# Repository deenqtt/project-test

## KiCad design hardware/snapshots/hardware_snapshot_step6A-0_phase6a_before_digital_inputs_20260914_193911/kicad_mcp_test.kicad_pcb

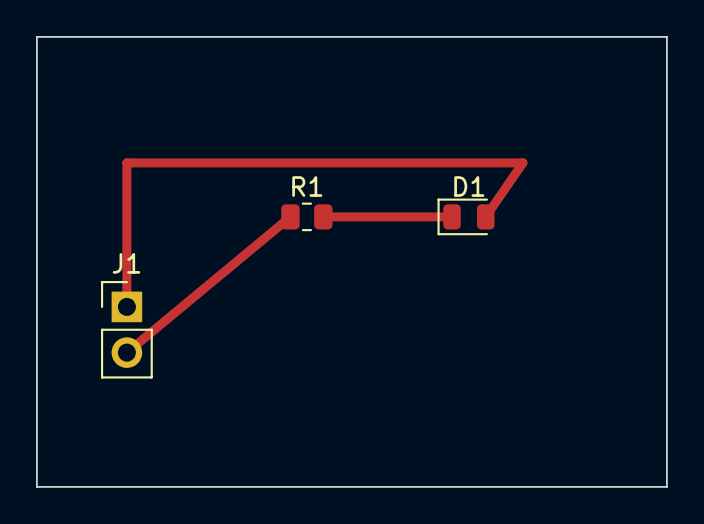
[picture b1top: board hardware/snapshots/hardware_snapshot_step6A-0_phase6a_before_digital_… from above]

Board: 2 copper layers, 35.0 x 25.0 mm, 3 parts (0 on the bottom side), 3 nets.

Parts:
D1: LED; LED_0805_2012Metric
J1: INPUT; PinHeader_1x02_P2.54mm_Vertical
R1: 1k; R_0805_2012Metric

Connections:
unnamed: D1.1, R1.2
unnamed: D1.2, J1.1
unnamed: J1.2, R1.1

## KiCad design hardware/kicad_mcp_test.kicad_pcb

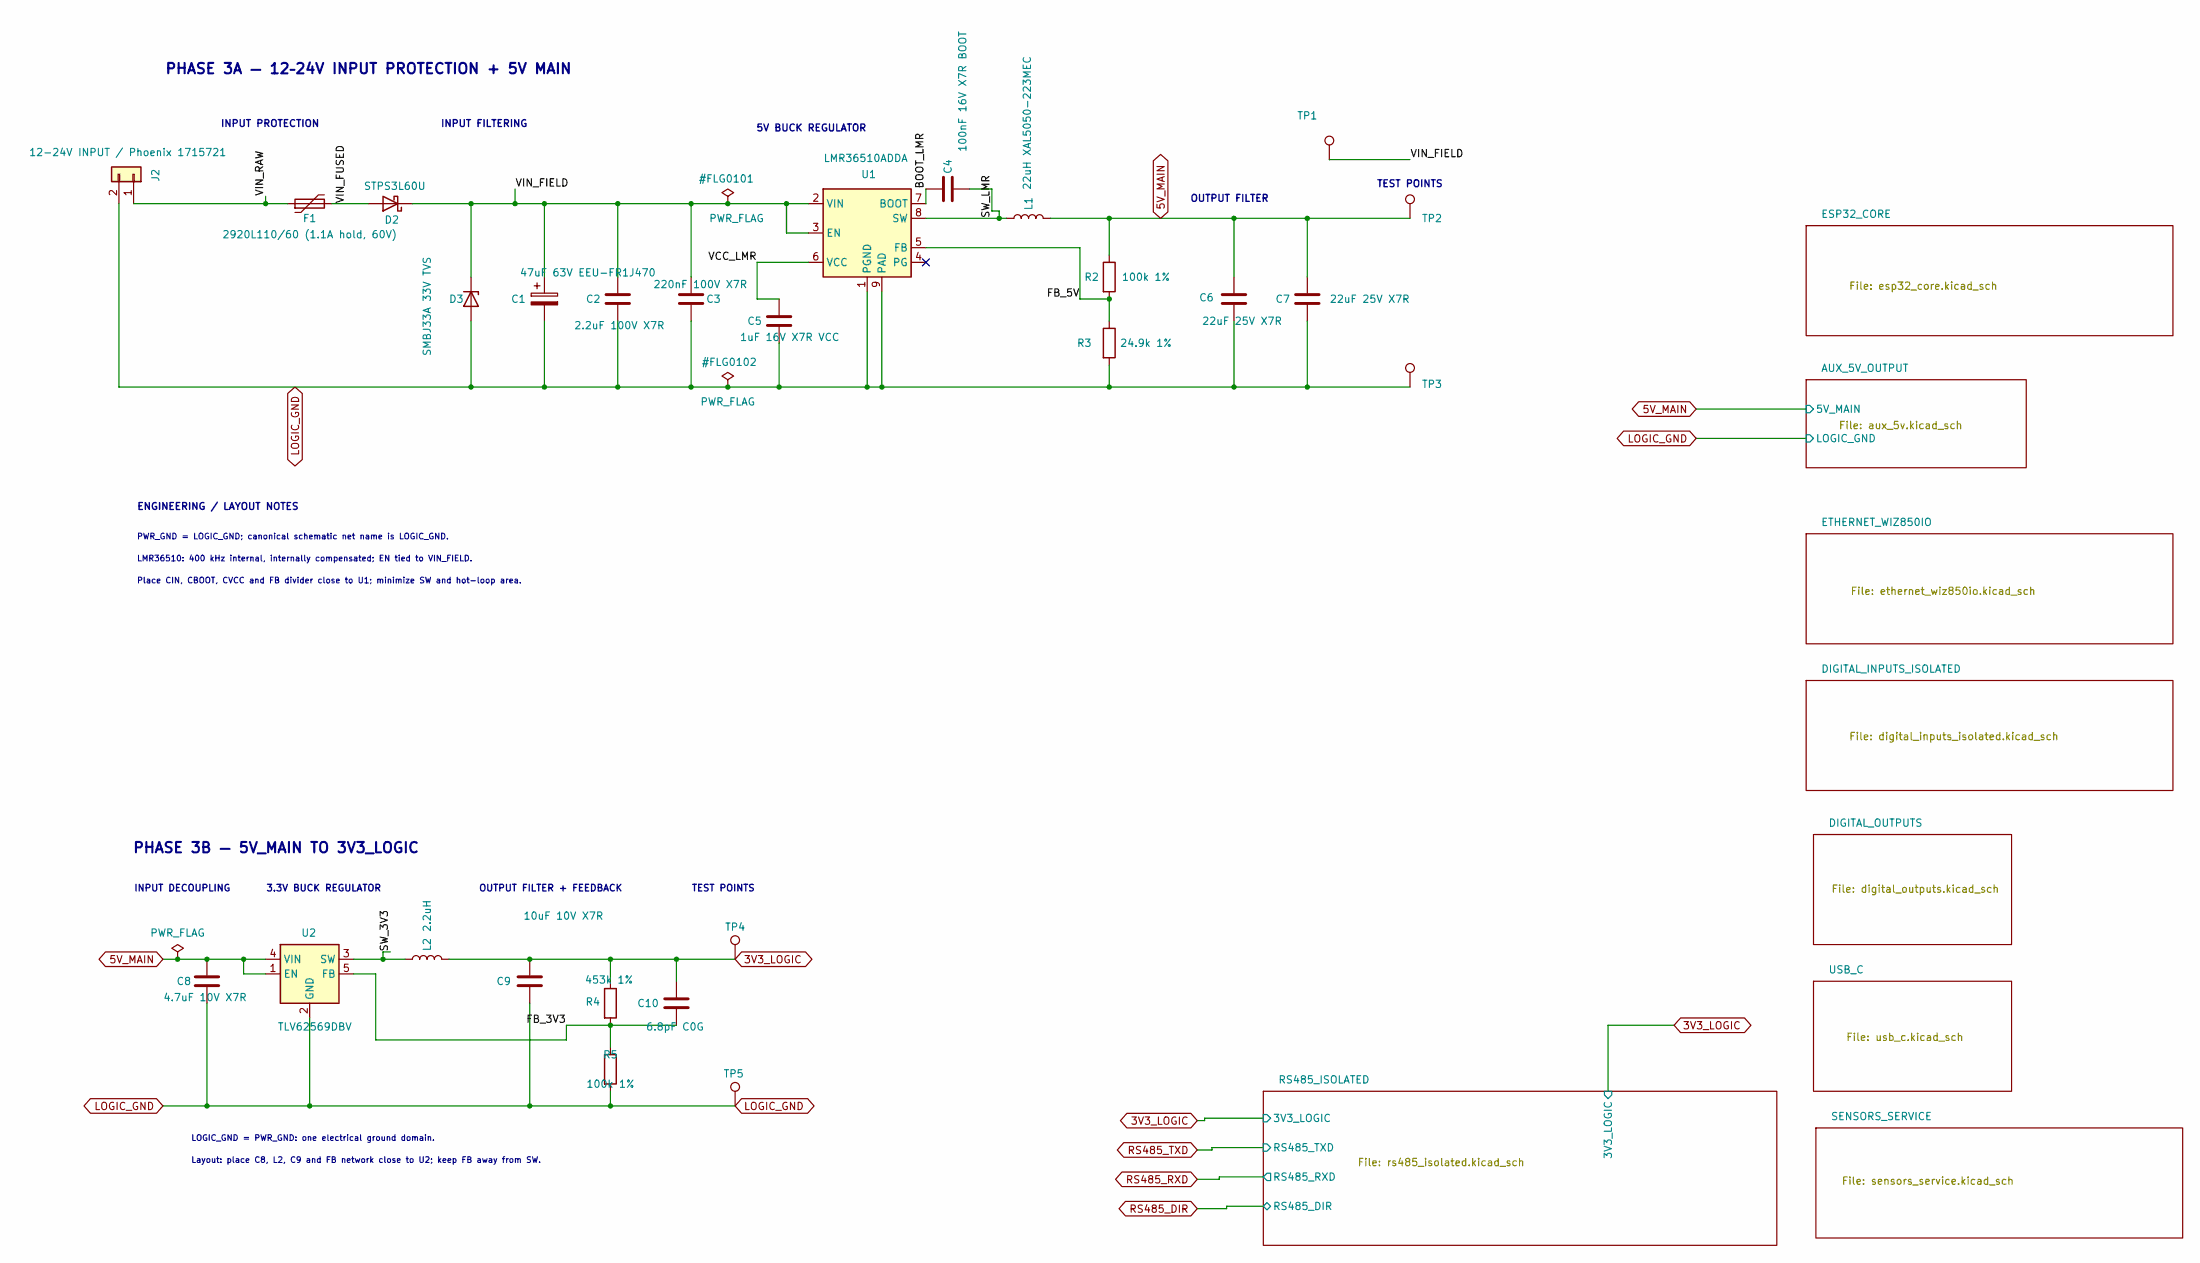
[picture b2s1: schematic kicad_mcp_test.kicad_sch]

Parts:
C1: 47uF 63V EEU-FR1J470; C_Radial_D6.3mm_H11.0mm_P2.50mm; MPN EEU-FR1J470
C2: 2.2uF 100V X7R; C_1210_3225Metric; Voltage 100V
C3: 220nF 100V X7R; C_0805_2012Metric; Voltage 100V
C4: 100nF 16V X7R BOOT; C_0603_1608Metric; Voltage 16V min
C5: 1uF 16V X7R VCC; C_0603_1608Metric; Voltage 16V
C6, C7: 22uF 25V X7R; C_1210_3225Metric; Voltage 25V
C8: 4.7uF 10V X7R; C_0805_2012Metric; Voltage 10V; MPN GRM21BR71A475KA73L
C9: 10uF 10V X7R; C_0805_2012Metric; Voltage 10V; MPN GRM21BR71A106KE51L
C10: 6.8pF C0G; C_0603_1608Metric; Voltage 50V
D2: STPS3L60U; D_SMB; MPN STPS3L60U
D3: SMBJ33A 33V TVS; D_SMB; MPN SMBJ33A
F1: 2920L110/60 (1.1A hold, 60V); Fuse_2920_7451Metric; MPN 2920L110/60MR
J2: 12-24V INPUT / Phoenix 1715721; TerminalBlock_Phoenix_MKDS-1,5-2-5.08_1x02_P5.08mm_Horizont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; MPN 1715721
L1: 22uH XAL5050-223MEC; L_Coilcraft_XAL5050-XXX; MPN XAL5050-223MEC
L2: 2.2uH; L_Coilcraft_XAL4020-XXX; MPN XAL4020-222MEC
R2: 100k 1%; R_0603_1608Metric; Tolerance 1%
R3: 24.9k 1%; R_0603_1608Metric; Tolerance 1%
R4: 453k 1%; R_0603_1608Metric
R5: 100k 1%; R_0603_1608Metric
TP1: VIN_FIELD; TestPoint_Pad_D2.5mm
TP2: 5V_MAIN; TestPoint_Pad_D2.5mm
TP3: PWR_GND; TestPoint_Pad_D2.5mm
TP4: 3V3_LOGIC; TestPoint_Pad_D2.5mm
TP5: LOGIC_GND; TestPoint_Pad_D2.5mm
U1: LMR36510ADDA; Texas_HTSOP-8-1EP_3.9x4.9mm_P1.27mm_EP2.95x4.9mm_Mask2.4x3.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; MPN LMR36510ADDA
U2: TLV62569DBV; SOT-23-5; MPN TLV62569DBV

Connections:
3V3_LOGIC: C9.1, C10.1, L2.2, R4.1, TP4.1; also elsewhere on the board
5V_MAIN: C6.1, C7.1, C8.1, L1.2, R2.1, TP2.1, U2.1 (EN), U2.4 (VIN); also elsewhere on the board
/BOOT_LMR: C4.1, U1.7 (BOOT)
/FB_3V3: C10.2, R4.2, R5.1, U2.5 (FB)
/FB_5V: R2.2, R3.1, U1.5 (FB)
/SW_3V3: L2.1, U2.3 (SW)
/SW_LMR: C4.2, L1.1, U1.8 (SW)
/VCC_LMR: C5.1, U1.6 (VCC)
/VIN_FIELD: C1.1, C2.1, C3.1, D2.1 (K), D3.1 (K), TP1.1, U1.2 (VIN), U1.3 (EN)
/VIN_FUSED: D2.2 (A), F1.2
/VIN_RAW: F1.1, J2.1
LOGIC_GND: C1.2, C2.2, C3.2, C5.2, C6.2, C7.2, C8.2, C9.2, D3.2 (A), J2.2, R3.2, R5.2, TP3.1, TP5.1, U1.1 (PGND), U1.9 (PAD), U2.2 (GND); also elsewhere on the board

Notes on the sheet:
TEST POINTS
LMR36510: 400 kHz internal, internally compensated; EN tied to VIN_FIELD.
INPUT FILTERING
ENGINEERING / LAYOUT NOTES
LOGIC_GND = PWR_GND: one electrical ground domain.
5V BUCK REGULATOR
PHASE 3A — 12–24V INPUT PROTECTION + 5V MAIN
PHASE 3B — 5V_MAIN TO 3V3_LOGIC
3.3V BUCK REGULATOR
INPUT PROTECTION
OUTPUT FILTER
OUTPUT FILTER + FEEDBACK
Place CIN, CBOOT, CVCC and FB divider close to U1; minimize SW and hot-loop area.
INPUT DECOUPLING
PWR_GND = LOGIC_GND; canonical schematic net name is LOGIC_GND.
Layout: place C8, L2, C9 and FB network close to U2; keep FB away from SW.

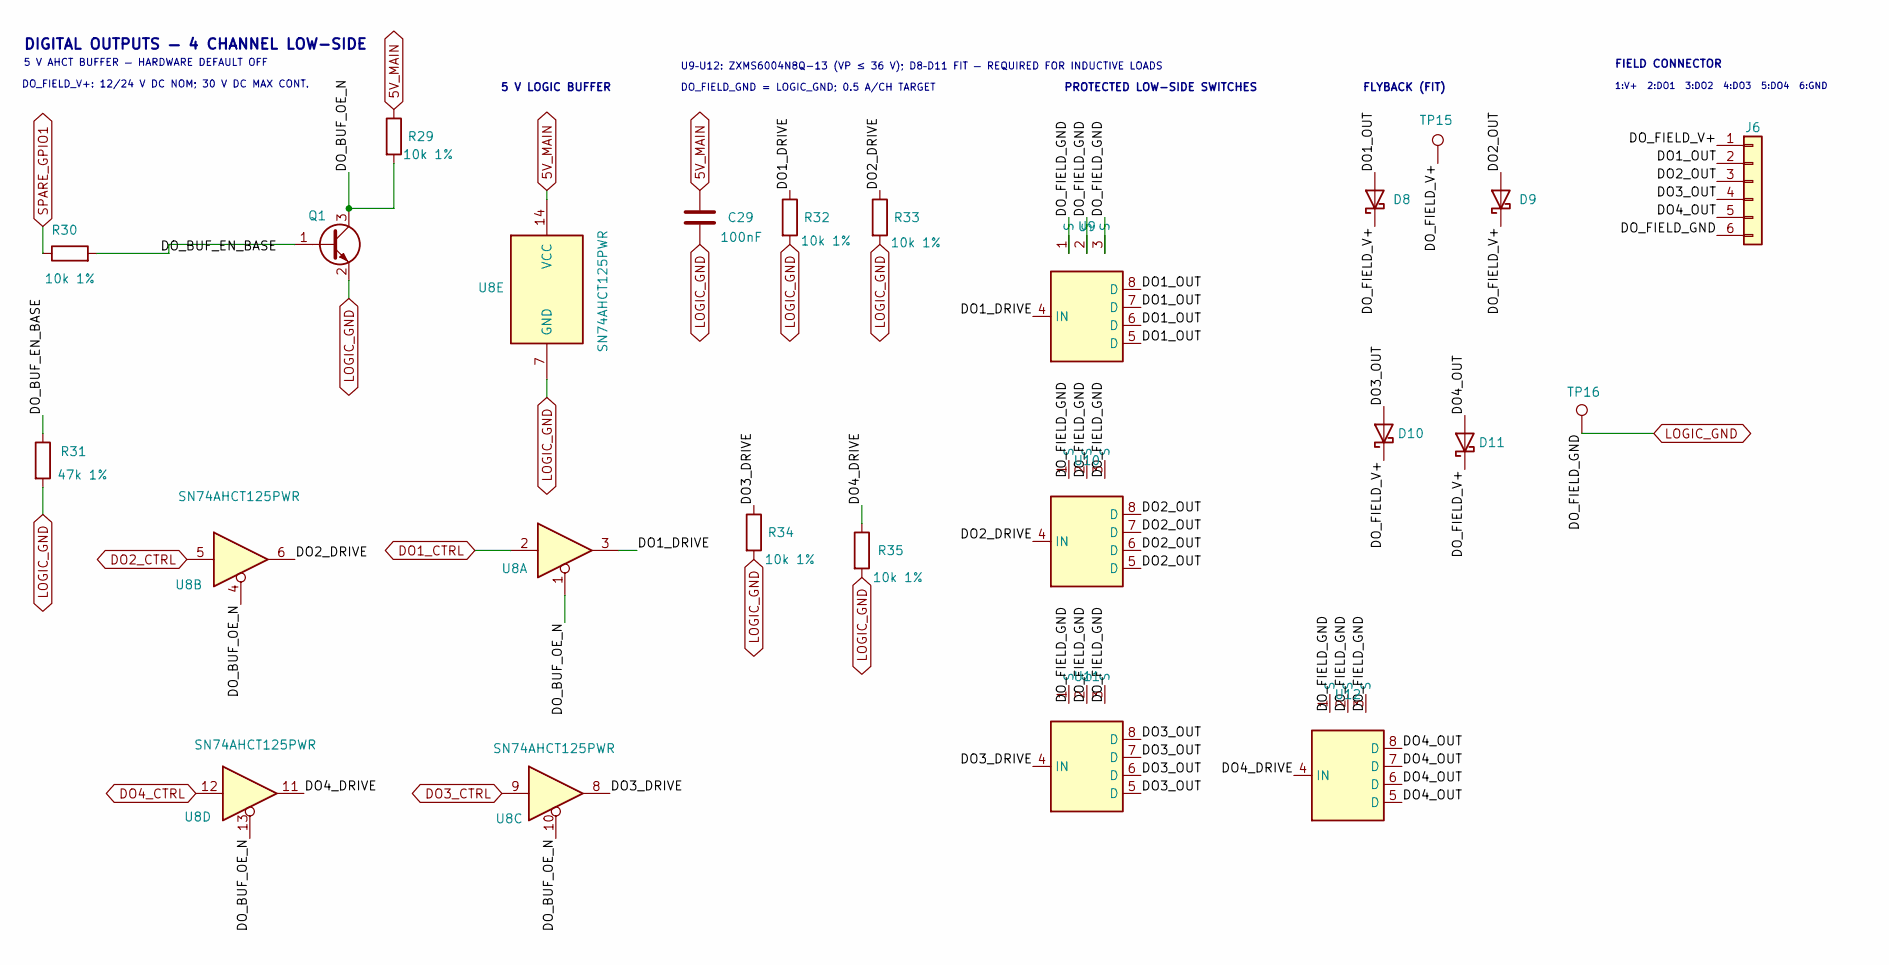
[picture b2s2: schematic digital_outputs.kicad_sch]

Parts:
C29: 100nF; C_0603_1608Metric; Voltage 16V
D8, D9, D10, D11: B360Q-13-F; D_SMC; MPN B360Q-13-F
J6: Phoenix 1706303; TerminalBlock_Phoenix_MKDS-1,5-6-5.08_1x06_P5.08mm_Horizont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; MPN 1706303
Q1: MMBT3904-7-F; SOT-23; MPN MMBT3904-7-F
R29, R30, R32, R33, R34, R35: 10k 1%; R_0603_1608Metric
R31: 47k 1%; R_0603_1608Metric
TP15: DO_FIELD_V+; TestPoint_Pad_D1.0mm
TP16: DO_FIELD_GND; TestPoint_Pad_D1.0mm
U8: SN74AHCT125PWR; TSSOP-14_4.4x5mm_P0.65mm
U9, U10, U11, U12: ZXMS6004N8Q-13; SOIC-8_3.9x4.9mm_P1.27mm; MPN ZXMS6004N8Q-13

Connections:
5V_MAIN: C29.1, R29.1, U8.14 (VCC); also elsewhere on the board
/DIGITAL_OUTPUTS/DO1_DRIVE: R32.1, U8.3, U9.4 (IN)
/DIGITAL_OUTPUTS/DO1_OUT: D8.2 (A), J6.2, U9.5 (D), U9.6 (D), U9.7 (D), U9.8 (D)
/DIGITAL_OUTPUTS/DO2_DRIVE: R33.1, U8.6, U10.4 (IN)
/DIGITAL_OUTPUTS/DO2_OUT: D9.2 (A), J6.3, U10.5 (D), U10.6 (D), U10.7 (D), U10.8 (D)
/DIGITAL_OUTPUTS/DO3_DRIVE: R34.1, U8.8, U11.4 (IN)
/DIGITAL_OUTPUTS/DO3_OUT: D10.2 (A), J6.4, U11.5 (D), U11.6 (D), U11.7 (D), U11.8 (D)
/DIGITAL_OUTPUTS/DO4_DRIVE: R35.1, U8.11, U12.4 (IN)
/DIGITAL_OUTPUTS/DO4_OUT: D11.2 (A), J6.5, U12.5 (D), U12.6 (D), U12.7 (D), U12.8 (D)
/DIGITAL_OUTPUTS/DO_BUF_EN_BASE: Q1.1 (B), R30.2, R31.1
/DIGITAL_OUTPUTS/DO_BUF_OE_N: Q1.3 (C), R29.2, U8.1, U8.4, U8.10, U8.13
/DIGITAL_OUTPUTS/DO_FIELD_V+: D8.1 (K), D9.1 (K), D10.1 (K), D11.1 (K), J6.1, TP15.1
DO1_CTRL: U8.2; also elsewhere on the board
DO2_CTRL: U8.5; also elsewhere on the board
DO3_CTRL: U8.9; also elsewhere on the board
DO4_CTRL: U8.12; also elsewhere on the board
LOGIC_GND: C29.2, J6.6, Q1.2 (E), R31.2, R32.2, R33.2, R34.2, R35.2, TP16.1, U8.7 (GND), U9.1 (S), U9.2 (S), U9.3 (S), U10.1 (S), U10.2 (S), U10.3 (S), U11.1 (S), U11.2 (S), U11.3 (S), U12.1 (S), U12.2 (S), U12.3 (S); also elsewhere on the board
SPARE_GPIO1: R30.1; also elsewhere on the board

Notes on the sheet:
U9–U12: ZXMS6004N8Q-13 (VP ≤ 36 V); D8–D11 FIT — REQUIRED FOR INDUCTIVE LOADS
5 V AHCT BUFFER — HARDWARE DEFAULT OFF
FLYBACK (FIT)
5 V LOGIC BUFFER
PROTECTED LOW-SIDE SWITCHES
1:V+ 2:DO1 3:DO2 4:DO3 5:DO4 6:GND
DO_FIELD_GND = LOGIC_GND; 0.5 A/CH TARGET
DIGITAL OUTPUTS — 4 CHANNEL LOW-SIDE
FIELD CONNECTOR
DO_FIELD_V+: 12/24 V DC NOM; 30 V DC MAX CONT.

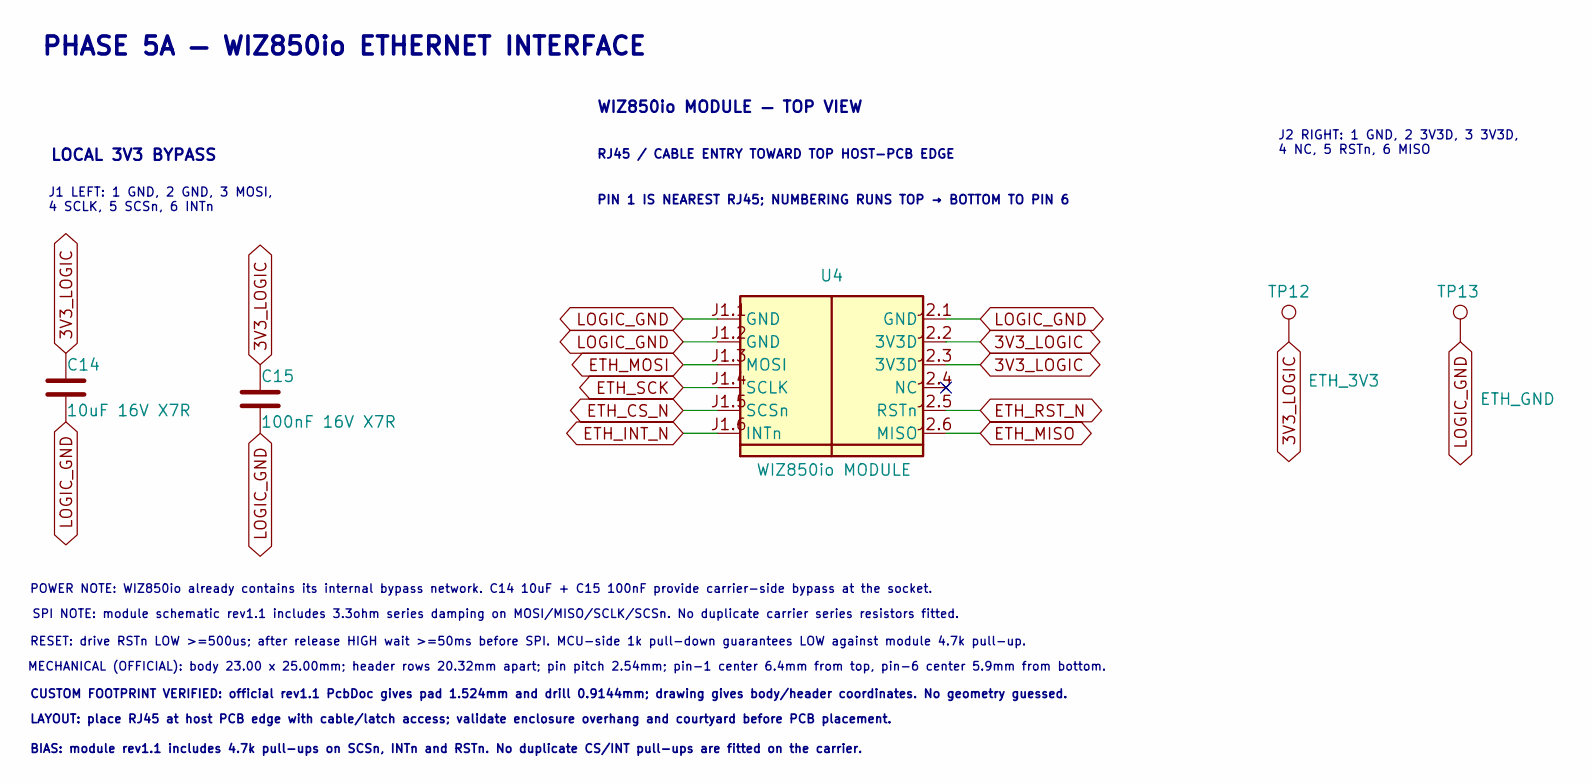
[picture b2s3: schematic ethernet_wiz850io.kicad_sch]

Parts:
C14: 10uF 16V X7R; C_1206_3216Metric; Voltage 16V
C15: 100nF 16V X7R; C_0603_1608Metric; Voltage 16V
TP12: ETH_3V3; TestPoint_Pad_D1.0mm
TP13: ETH_GND; TestPoint_Pad_D1.0mm
U4: WIZ850io MODULE; WIZ850io_Module_THT; MPN WIZ850io

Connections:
3V3_LOGIC: C14.1, C15.1, TP12.1, U4.J2.2 (3V3D), U4.J2.3 (3V3D); also elsewhere on the board
ETH_CS_N: U4.J1.5 (SCSn); also elsewhere on the board
ETH_INT_N: U4.J1.6 (INTn); also elsewhere on the board
ETH_MISO: U4.J2.6 (MISO); also elsewhere on the board
ETH_MOSI: U4.J1.3 (MOSI); also elsewhere on the board
ETH_RST_N: U4.J2.5 (RSTn); also elsewhere on the board
ETH_SCK: U4.J1.4 (SCLK); also elsewhere on the board
LOGIC_GND: C14.2, C15.2, TP13.1, U4.J1.1 (GND), U4.J1.2 (GND), U4.J2.1 (GND); also elsewhere on the board

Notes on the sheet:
MECHANICAL (OFFICIAL): body 23.00 x 25.00mm; header rows 20.32mm apart; pin pitch 2.54mm; pin-1 center 6.4mm from top, pin-6 center 5.9mm from bottom.
RJ45 / CABLE ENTRY TOWARD TOP HOST-PCB EDGE
LOCAL 3V3 BYPASS
CUSTOM FOOTPRINT VERIFIED: official rev1.1 PcbDoc gives pad 1.524mm and drill 0.9144mm; drawing gives body/header coordinates. No geometry guessed.
BIAS: module rev1.1 includes 4.7k pull-ups on SCSn, INTn and RSTn. No duplicate CS/INT pull-ups are fitted on the carrier.
J1 LEFT: 1 GND, 2 GND, 3 MOSI, 4 SCLK, 5 SCSn, 6 INTn
PHASE 5A — WIZ850io ETHERNET INTERFACE
POWER NOTE: WIZ850io already contains its internal bypass network. C14 10uF + C15 100nF provide carrier-side bypass at the socket.
J2 RIGHT: 1 GND, 2 3V3D, 3 3V3D, 4 NC, 5 RSTn, 6 MISO
PIN 1 IS NEAREST RJ45; NUMBERING RUNS TOP → BOTTOM TO PIN 6
RESET: drive RSTn LOW >=500us; after release HIGH wait >=50ms before SPI. MCU-side 1k pull-down guarantees LOW against module 4.7k pull-up.
WIZ850io MODULE — TOP VIEW
SPI NOTE: module schematic rev1.1 includes 3.3ohm series damping on MOSI/MISO/SCLK/SCSn. No duplicate carrier series resistors fitted.
LAYOUT: place RJ45 at host PCB edge with cable/latch access; validate enclosure overhang and courtyard before PCB placement.

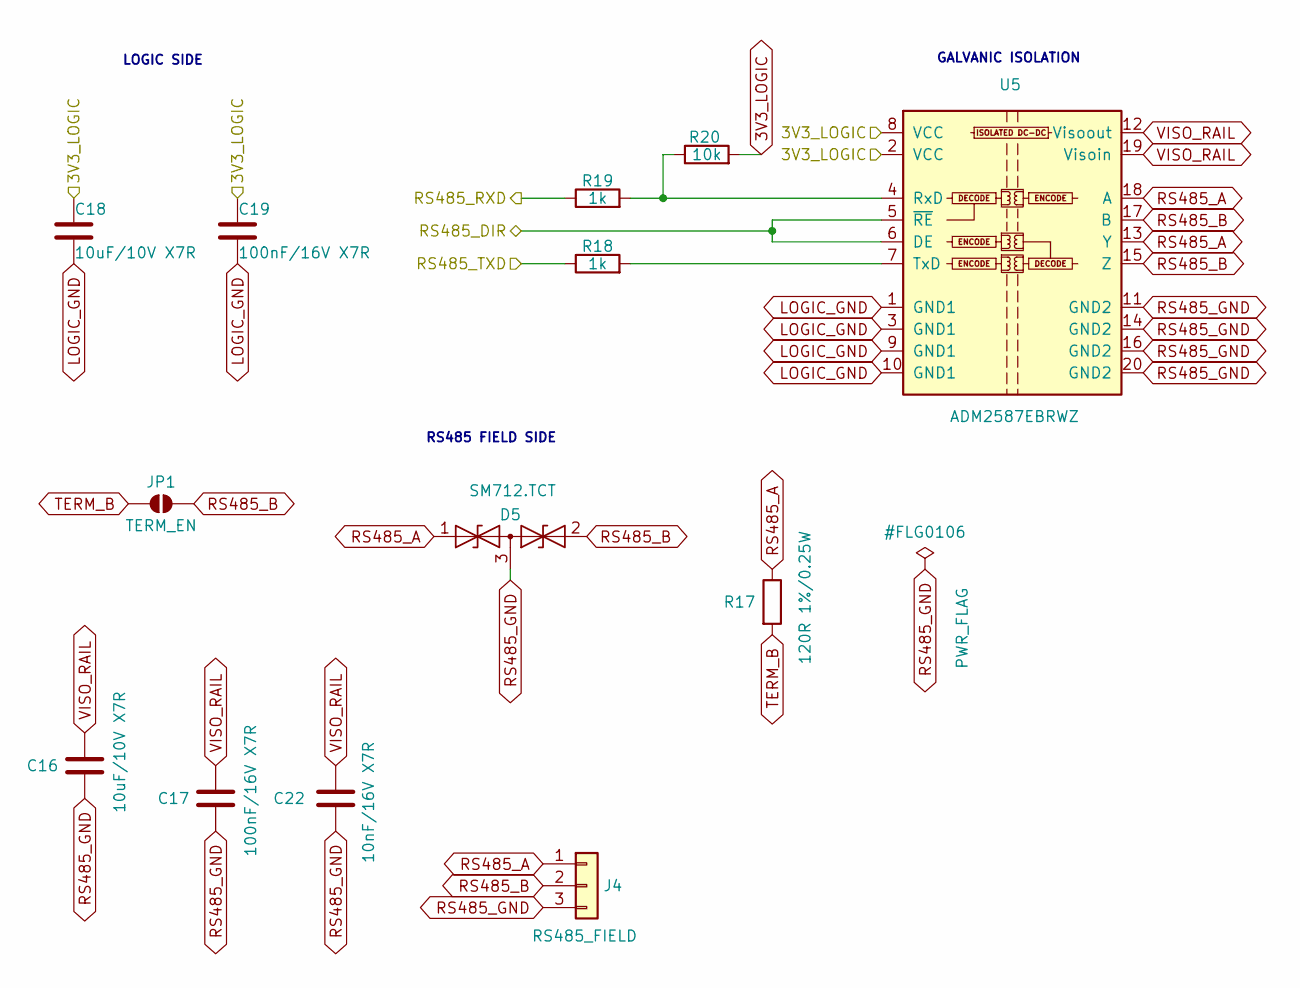
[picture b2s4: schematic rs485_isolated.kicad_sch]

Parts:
C16, C18: 10uF/10V X7R; C_0805_2012Metric; MPN GRM21BR71A106KE51K
C17, C19: 100nF/16V X7R; C_0402_1005Metric; MPN GRM21BR71H104KA01L
C22: 10nF/16V X7R; C_0402_1005Metric; MPN GRM21BR71H104KA01L
D5: SM712.TCT; SOT-23; MPN SM712.TCT
J4: RS485_FIELD; TerminalBlock_Phoenix_MKDS-1,5-3-5.08_1x03_P5.08mm_Horizont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; MPN 1715734
JP1: TERM_EN; SolderJumper-2_P1.3mm_Open_Pad1.0x1.5mm
R17: 120R 1%/0.25W; R_0805_2012Metric
R18, R19: 1k; R_0805_2012Metric
R20: 10k; R_0805_2012Metric
U5: ADM2587EBRWZ; SOIC-20W_7.5x12.8mm_P1.27mm; MPN ADM2587EBRWZ

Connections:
3V3_LOGIC: C18.1, C19.1, R20.2, U5.2 (VCC), U5.8 (VCC); also elsewhere on the board
LOGIC_GND: C18.2, C19.2, U5.1 (GND1), U5.3 (GND1), U5.9 (GND1), U5.10 (GND1); also elsewhere on the board
unnamed: R19.2, R20.1, U5.4 (RxD)
unnamed: R18.2, U5.7 (TxD)
RS485_A: D5.1 (A1), J4.1, R17.1, U5.13 (Y), U5.18 (A)
RS485_B: D5.2 (A2), J4.2, JP1.2 (B), U5.15 (Z), U5.17 (B)
RS485_DIR: U5.5 (~RE), U5.6 (DE); also elsewhere on the board
RS485_GND: C16.2, C17.2, C22.2, D5.3 (common), J4.3, U5.11 (GND2), U5.14 (GND2), U5.16 (GND2), U5.20 (GND2)
RS485_RXD: R19.1; also elsewhere on the board
RS485_TXD: R18.1; also elsewhere on the board
TERM_B: JP1.1 (A), R17.2
VISO_RAIL: C16.1, C17.1, C22.1, U5.12 (Visoout), U5.19 (Visoin)

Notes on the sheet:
LOGIC SIDE
RS485 FIELD SIDE
GALVANIC ISOLATION

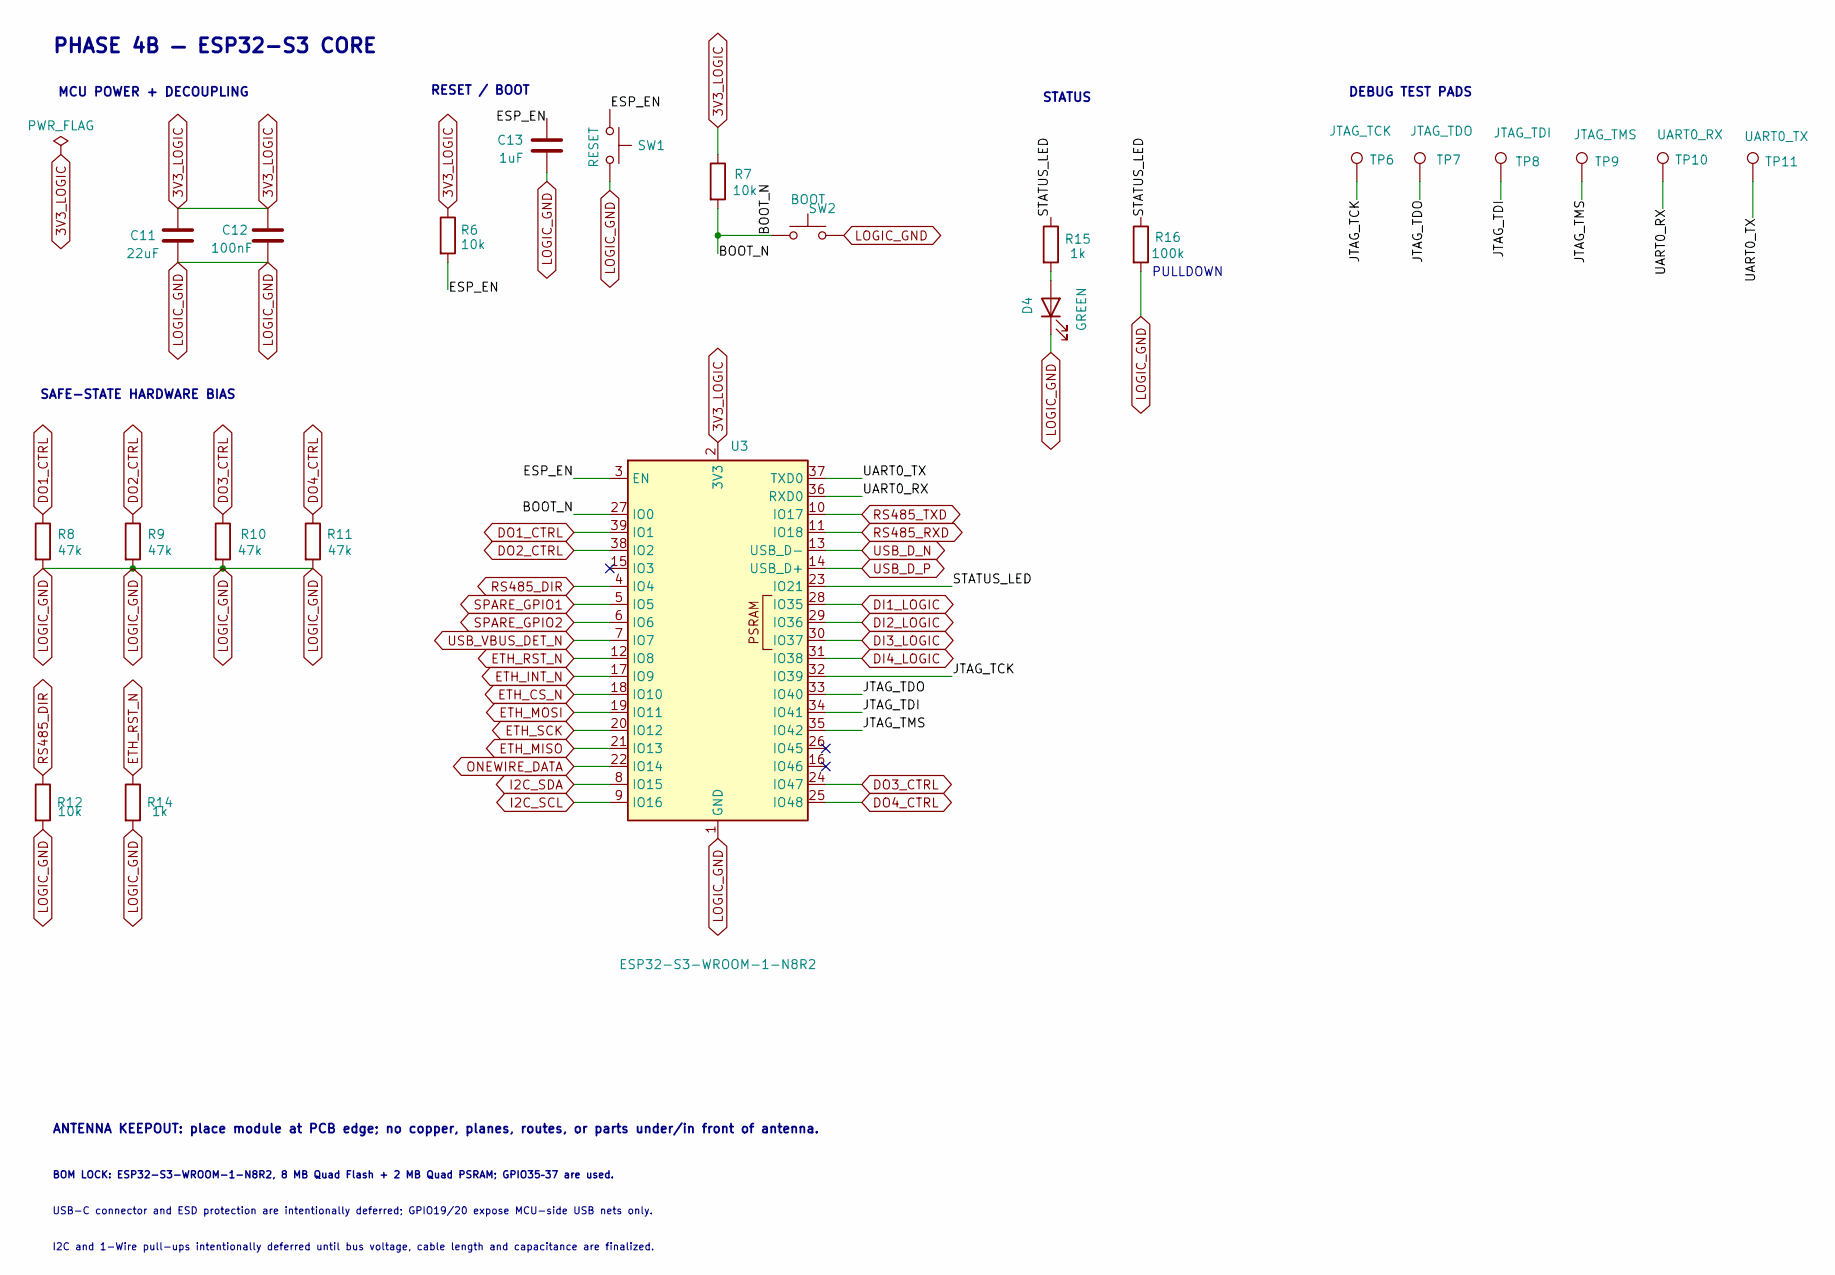
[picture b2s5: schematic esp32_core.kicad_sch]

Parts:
C11: 22uF; C_1206_3216Metric; Voltage 10 V
C12: 100nF; C_0603_1608Metric; Voltage 10 V
C13: 1uF; C_0603_1608Metric; Voltage 10 V
D4: GREEN; LED_0603_1608Metric; MPN LTST-C190KGKT
R6, R7, R12: 10k; R_0603_1608Metric
R8, R9, R10, R11: 47k; R_0603_1608Metric
R14, R15: 1k; R_0603_1608Metric
R16: 100k; R_0603_1608Metric
SW1: RESET; SW_PUSH_6mm; MPN B3F-1000
SW2: BOOT; SW_PUSH_6mm; MPN B3F-1000
TP6: JTAG_TCK; TestPoint_Pad_D1.0mm
TP7: JTAG_TDO; TestPoint_Pad_D1.0mm
TP8: JTAG_TDI; TestPoint_Pad_D1.0mm
TP9: JTAG_TMS; TestPoint_Pad_D1.0mm
TP10: UART0_RX; TestPoint_Pad_D1.0mm
TP11: UART0_TX; TestPoint_Pad_D1.0mm
U3: ESP32-S3-WROOM-1-N8R2; ESP32-S3-WROOM-1; MPN ESP32-S3-WROOM-1-N8R2

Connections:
3V3_LOGIC: C11.1, C12.1, R6.1, R7.1, U3.2 (3V3); also elsewhere on the board
/ESP32_CORE/BOOT_N: R7.2, SW2.1, U3.27 (IO0)
/ESP32_CORE/ESP_EN: C13.1, R6.2, SW1.1, U3.3 (EN)
/ESP32_CORE/JTAG_TCK: TP6.1, U3.32 (IO39)
/ESP32_CORE/JTAG_TDI: TP8.1, U3.34 (IO41)
/ESP32_CORE/JTAG_TDO: TP7.1, U3.33 (IO40)
/ESP32_CORE/JTAG_TMS: TP9.1, U3.35 (IO42)
/ESP32_CORE/STATUS_LED: R15.1, R16.1, U3.23 (IO21)
/ESP32_CORE/UART0_RX: TP10.1, U3.36 (RXD0)
/ESP32_CORE/UART0_TX: TP11.1, U3.37 (TXD0)
DI1_LOGIC: U3.28 (IO35); also elsewhere on the board
DI2_LOGIC: U3.29 (IO36); also elsewhere on the board
DI3_LOGIC: U3.30 (IO37); also elsewhere on the board
DI4_LOGIC: U3.31 (IO38); also elsewhere on the board
DO1_CTRL: R8.1, U3.39 (IO1); also elsewhere on the board
DO2_CTRL: R9.1, U3.38 (IO2); also elsewhere on the board
DO3_CTRL: R10.1, U3.24 (IO47); also elsewhere on the board
DO4_CTRL: R11.1, U3.25 (IO48); also elsewhere on the board
ETH_CS_N: U3.18 (IO10); also elsewhere on the board
ETH_INT_N: U3.17 (IO9); also elsewhere on the board
ETH_MISO: U3.21 (IO13); also elsewhere on the board
ETH_MOSI: U3.19 (IO11); also elsewhere on the board
ETH_RST_N: R14.1, U3.12 (IO8); also elsewhere on the board
ETH_SCK: U3.20 (IO12); also elsewhere on the board
I2C_SCL: U3.9 (IO16); also elsewhere on the board
I2C_SDA: U3.8 (IO15); also elsewhere on the board
LOGIC_GND: C11.2, C12.2, C13.2, D4.1 (K), R8.2, R9.2, R10.2, R11.2, R12.2, R14.2, R16.2, SW1.2, SW2.2, U3.1 (GND), U3.40 (GND), U3.41 (GND); also elsewhere on the board
unnamed: D4.2 (A), R15.2
ONEWIRE_DATA: U3.22 (IO14); also elsewhere on the board
RS485_DIR: R12.1, U3.4 (IO4); also elsewhere on the board
RS485_RXD: U3.11 (IO18); also elsewhere on the board
RS485_TXD: U3.10 (IO17); also elsewhere on the board
SPARE_GPIO1: U3.5 (IO5); also elsewhere on the board
SPARE_GPIO2: U3.6 (IO6); also elsewhere on the board
USB_D_N: U3.13 (USB_D-); also elsewhere on the board
USB_D_P: U3.14 (USB_D+); also elsewhere on the board
USB_VBUS_DET_N: U3.7 (IO7); also elsewhere on the board

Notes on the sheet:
MCU POWER + DECOUPLING
DEBUG TEST PADS
PULLDOWN
SAFE-STATE HARDWARE BIAS
STATUS
PHASE 4B — ESP32-S3 CORE
ANTENNA KEEPOUT: place module at PCB edge; no copper, planes, routes, or parts under/in front of antenna.
I2C and 1-Wire pull-ups intentionally deferred until bus voltage, cable length and capacitance are finalized.
USB-C connector and ESD protection are intentionally deferred; GPIO19/20 expose MCU-side USB nets only.
BOM LOCK: ESP32-S3-WROOM-1-N8R2, 8 MB Quad Flash + 2 MB Quad PSRAM; GPIO35–37 are used.
RESET / BOOT

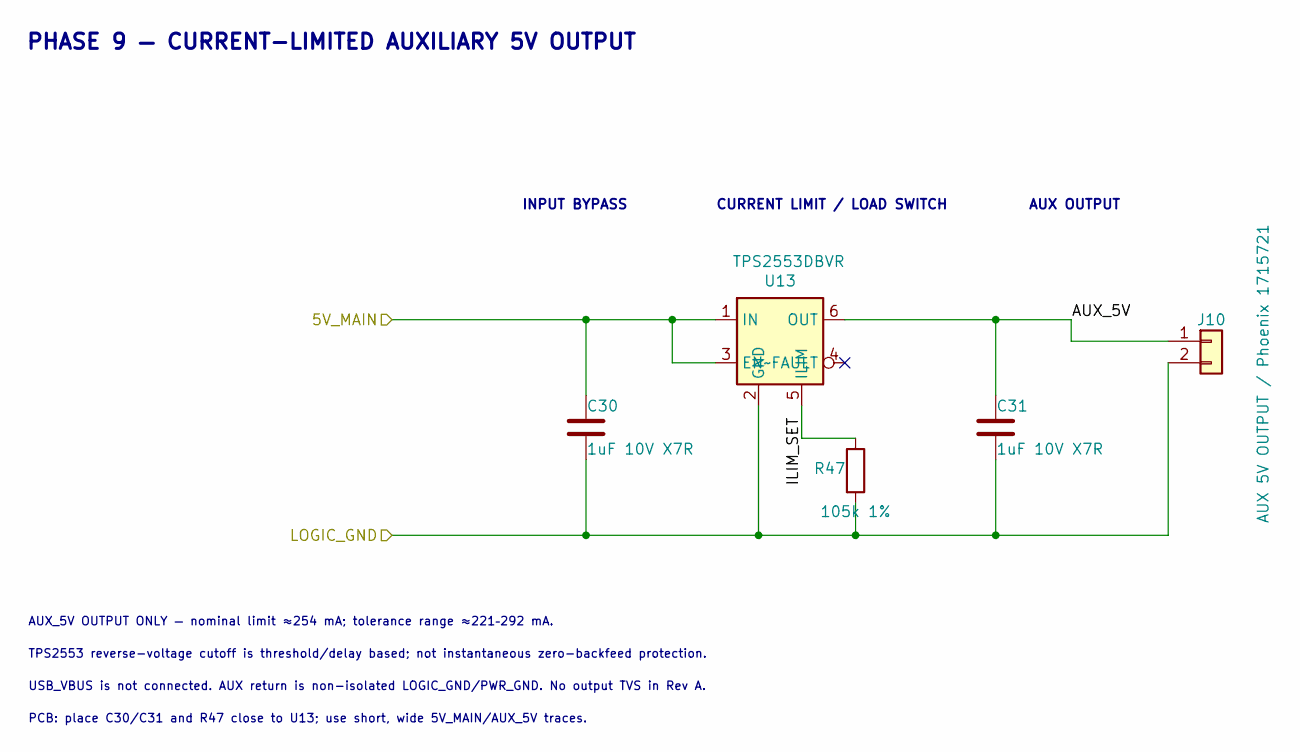
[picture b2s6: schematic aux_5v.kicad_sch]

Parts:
C30, C31: 1uF 10V X7R; C_0805_2012Metric; Voltage 10V
J10: AUX 5V OUTPUT / Phoenix 1715721; TerminalBlock_Phoenix_MKDS-1,5-2-5.08_1x02_P5.08mm_Horizont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; MPN 1715721
R47: 105k 1%; R_0603_1608Metric; Tolerance 1%
U13: TPS2553DBVR; SOT-23-6; MPN TPS2553DBVR

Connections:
5V_MAIN: C30.1, U13.1 (IN), U13.3 (EN); also elsewhere on the board
/AUX_5V_OUTPUT/AUX_5V: C31.1, J10.1, U13.6 (OUT)
/AUX_5V_OUTPUT/ILIM_SET: R47.1, U13.5 (ILIM)
LOGIC_GND: C30.2, C31.2, J10.2, R47.2, U13.2 (GND); also elsewhere on the board

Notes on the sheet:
PCB: place C30/C31 and R47 close to U13; use short, wide 5V_MAIN/AUX_5V traces.
INPUT BYPASS
AUX_5V OUTPUT ONLY — nominal limit ≈254 mA; tolerance range ≈221–292 mA.
PHASE 9 — CURRENT-LIMITED AUXILIARY 5V OUTPUT
USB_VBUS is not connected. AUX return is non-isolated LOGIC_GND/PWR_GND. No output TVS in Rev A.
TPS2553 reverse-voltage cutoff is threshold/delay based; not instantaneous zero-backfeed protection.
CURRENT LIMIT / LOAD SWITCH
AUX OUTPUT

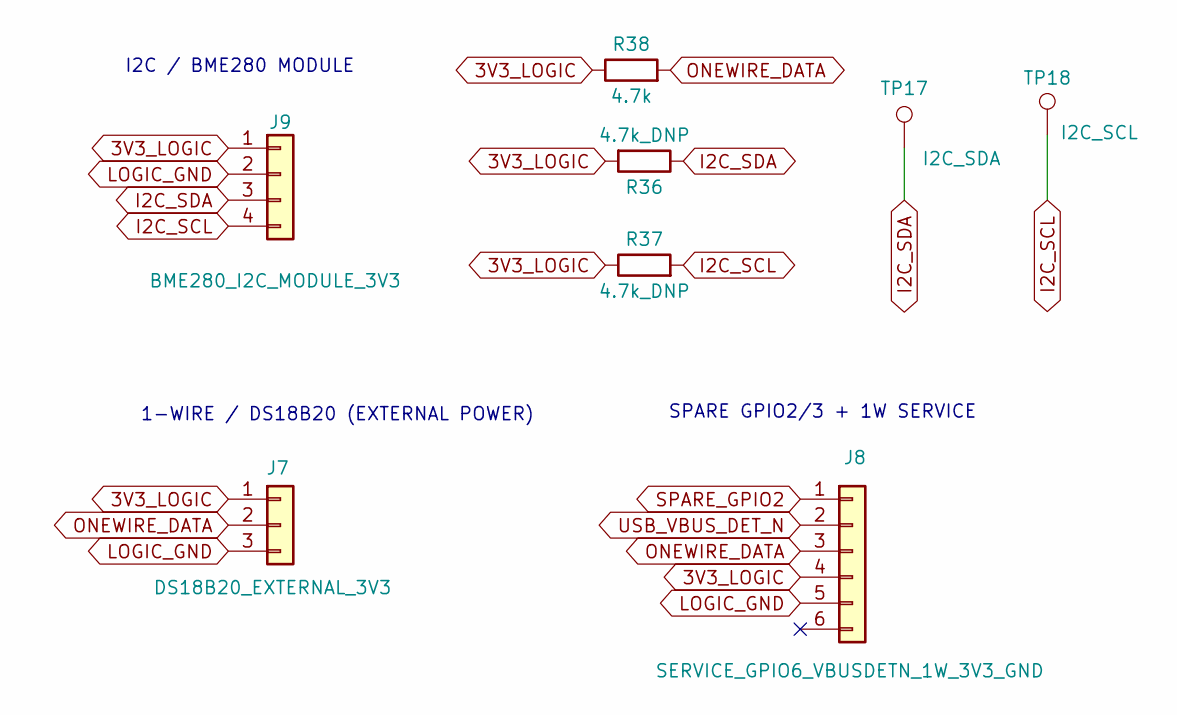
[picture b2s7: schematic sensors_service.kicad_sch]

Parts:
J7: DS18B20_EXTERNAL_3V3; PinHeader_1x03_P2.54mm_Vertical
J8: SERVICE_GPIO6_VBUSDETN_1W_3V3_GND; PinHeader_1x06_P2.54mm_Vertical
J9: BME280_I2C_MODULE_3V3; PinHeader_1x04_P2.54mm_Vertical
R36, R37: 4.7k_DNP; R_0603_1608Metric
R38: 4.7k; R_0603_1608Metric
TP17: I2C_SDA; TestPoint_Pad_D1.0mm
TP18: I2C_SCL; TestPoint_Pad_D1.0mm

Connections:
3V3_LOGIC: J7.1, J8.4, J9.1, R36.2, R37.1, R38.1; also elsewhere on the board
I2C_SCL: J9.4, R37.2, TP18.1; also elsewhere on the board
I2C_SDA: J9.3, R36.1, TP17.1; also elsewhere on the board
LOGIC_GND: J7.3, J8.5, J9.2; also elsewhere on the board
ONEWIRE_DATA: J7.2, J8.3, R38.2; also elsewhere on the board
SPARE_GPIO2: J8.1; also elsewhere on the board
USB_VBUS_DET_N: J8.2; also elsewhere on the board

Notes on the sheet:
I2C / BME280 MODULE
1-WIRE / DS18B20 (EXTERNAL POWER)
SPARE GPIO2/3 + 1W SERVICE

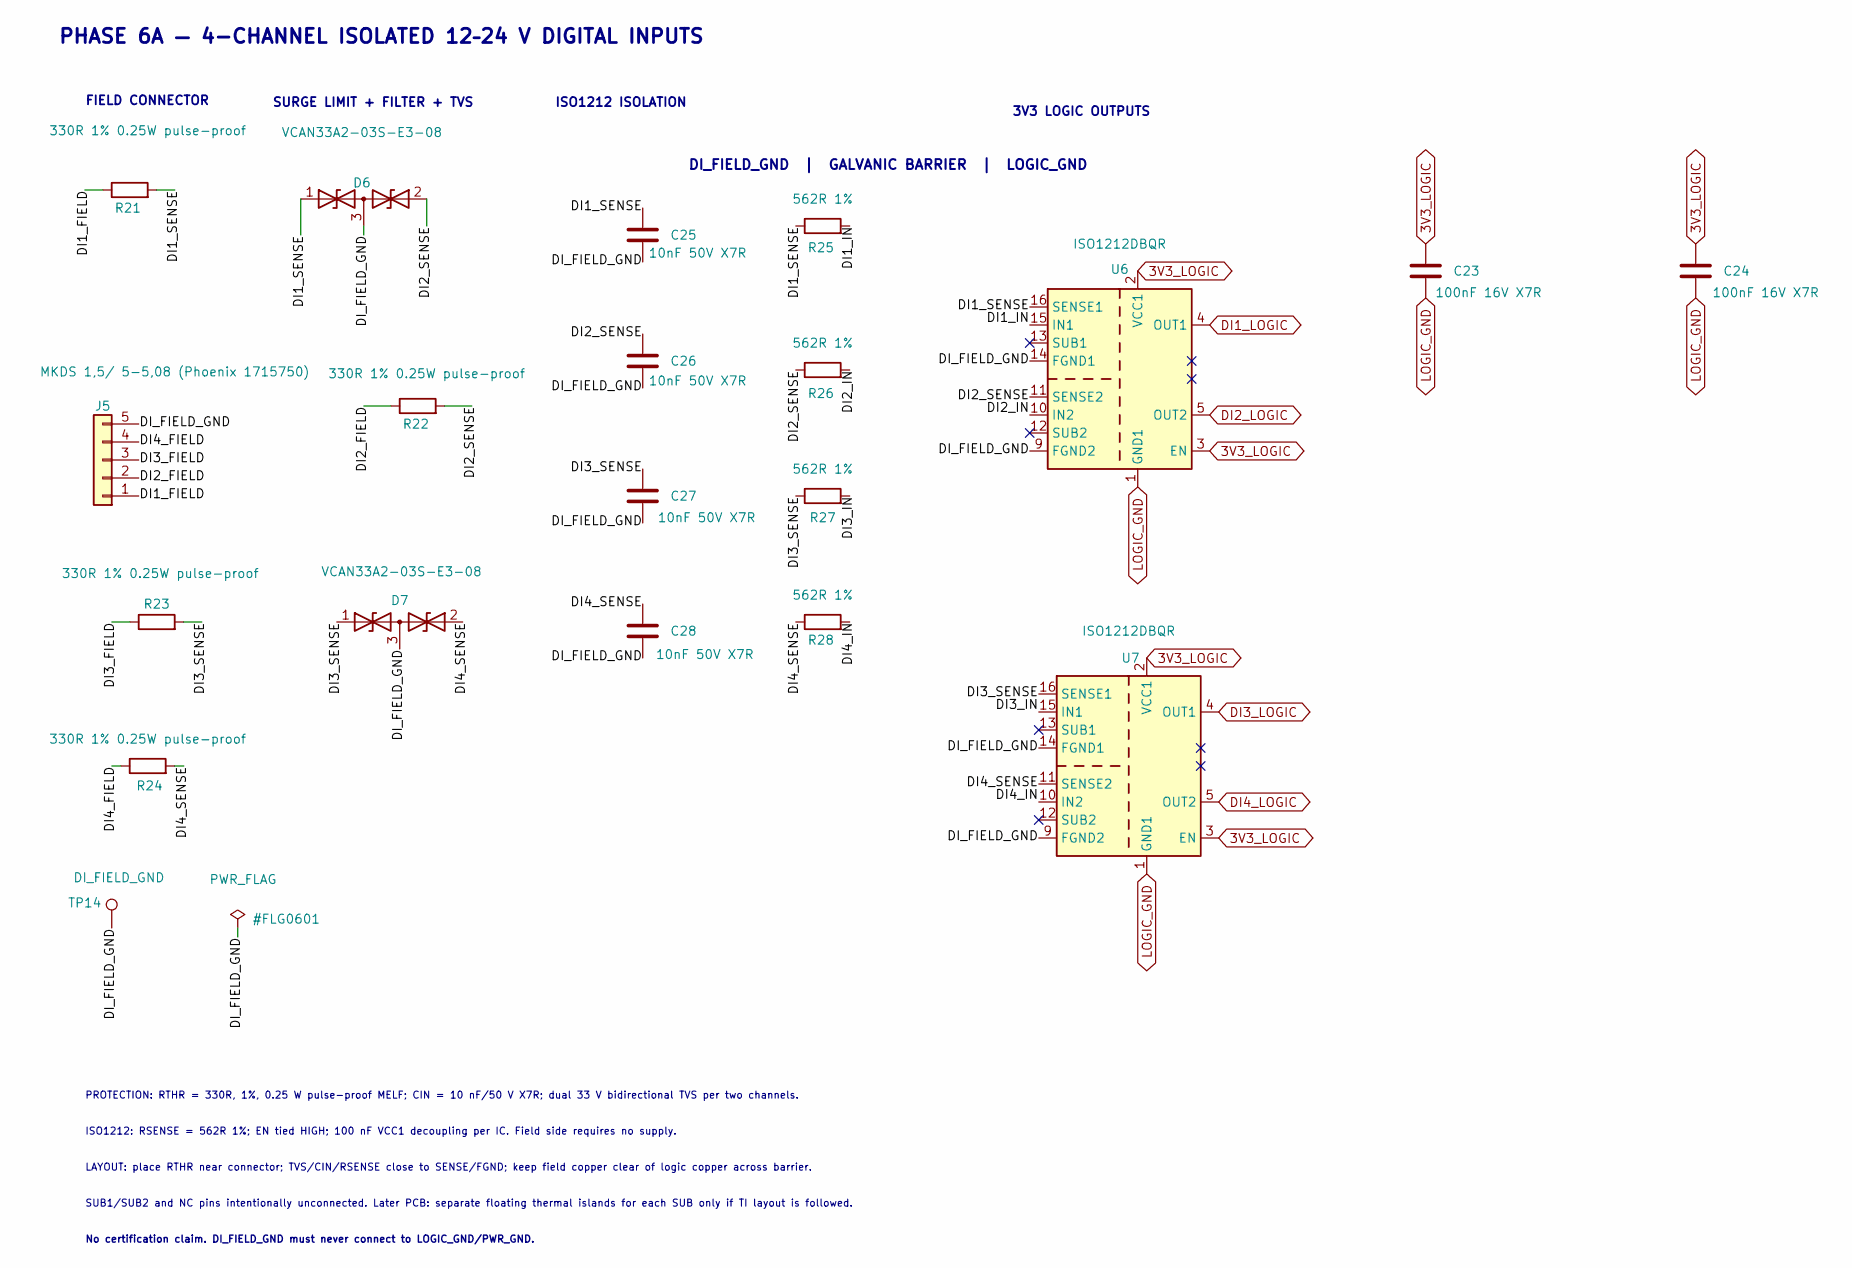
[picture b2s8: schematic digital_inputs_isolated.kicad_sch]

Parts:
C23, C24: 100nF 16V X7R; C_0603_1608Metric
C25, C26, C27, C28: 10nF 50V X7R; C_0603_1608Metric
D6, D7: VCAN33A2-03S-E3-08; SOT-23; MPN VCAN33A2-03S-E3-08
J5: MKDS 1,5/ 5-5,08 (Phoenix 1715750); TerminalBlock_Phoenix_MKDS-1,5-5-5.08_1x05_P5.08mm_Horizont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; MPN 1715750
R21, R22, R23, R24: 330R 1% 0.25W pulse-proof; R_MiniMELF_MMA-0204
R25, R26, R27, R28: 562R 1%; R_0603_1608Metric
TP14: DI_FIELD_GND; TestPoint_Pad_D1.0mm
U6, U7: ISO1212DBQR; SSOP-16_3.9x4.9mm_P0.635mm; MPN ISO1212DBQR

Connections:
3V3_LOGIC: C23.1, C24.1, U6.2 (VCC1), U6.3 (EN), U7.2 (VCC1), U7.3 (EN); also elsewhere on the board
/DIGITAL_INPUTS_ISOLATED/DI1_FIELD: J5.1, R21.1
/DIGITAL_INPUTS_ISOLATED/DI1_IN: R25.2, U6.15 (IN1)
/DIGITAL_INPUTS_ISOLATED/DI1_SENSE: C25.1, D6.1 (A1), R21.2, R25.1, U6.16 (SENSE1)
/DIGITAL_INPUTS_ISOLATED/DI2_FIELD: J5.2, R22.1
/DIGITAL_INPUTS_ISOLATED/DI2_IN: R26.2, U6.10 (IN2)
/DIGITAL_INPUTS_ISOLATED/DI2_SENSE: C26.1, D6.2 (A2), R22.2, R26.1, U6.11 (SENSE2)
/DIGITAL_INPUTS_ISOLATED/DI3_FIELD: J5.3, R23.1
/DIGITAL_INPUTS_ISOLATED/DI3_IN: R27.2, U7.15 (IN1)
/DIGITAL_INPUTS_ISOLATED/DI3_SENSE: C27.1, D7.1 (A1), R23.2, R27.1, U7.16 (SENSE1)
/DIGITAL_INPUTS_ISOLATED/DI4_FIELD: J5.4, R24.1
/DIGITAL_INPUTS_ISOLATED/DI4_IN: R28.2, U7.10 (IN2)
/DIGITAL_INPUTS_ISOLATED/DI4_SENSE: C28.1, D7.2 (A2), R24.2, R28.1, U7.11 (SENSE2)
/DIGITAL_INPUTS_ISOLATED/DI_FIELD_GND: C25.2, C26.2, C27.2, C28.2, D6.3 (common), D7.3 (common), J5.5, TP14.1, U6.9 (FGND2), U6.14 (FGND1), U7.9 (FGND2), U7.14 (FGND1)
DI1_LOGIC: U6.4 (OUT1); also elsewhere on the board
DI2_LOGIC: U6.5 (OUT2); also elsewhere on the board
DI3_LOGIC: U7.4 (OUT1); also elsewhere on the board
DI4_LOGIC: U7.5 (OUT2); also elsewhere on the board
LOGIC_GND: C23.2, C24.2, U6.1 (GND1), U6.8 (GND1), U7.1 (GND1), U7.8 (GND1); also elsewhere on the board

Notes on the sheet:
SURGE LIMIT + FILTER + TVS
3V3 LOGIC OUTPUTS
LAYOUT: place RTHR near connector; TVS/CIN/RSENSE close to SENSE/FGND; keep field copper clear of logic copper across barrier.
PROTECTION: RTHR = 330R, 1%, 0.25 W pulse-proof MELF; CIN = 10 nF/50 V X7R; dual 33 V bidirectional TVS per two channels.
DI_FIELD_GND | GALVANIC BARRIER | LOGIC_GND
ISO1212 ISOLATION
FIELD CONNECTOR
SUB1/SUB2 and NC pins intentionally unconnected. Later PCB: separate floating thermal islands for each SUB only if TI layout is followed.
PHASE 6A — 4-CHANNEL ISOLATED 12–24 V DIGITAL INPUTS
ISO1212: RSENSE = 562R 1%; EN tied HIGH; 100 nF VCC1 decoupling per IC. Field side requires no supply.
No certification claim. DI_FIELD_GND must never connect to LOGIC_GND/PWR_GND.
